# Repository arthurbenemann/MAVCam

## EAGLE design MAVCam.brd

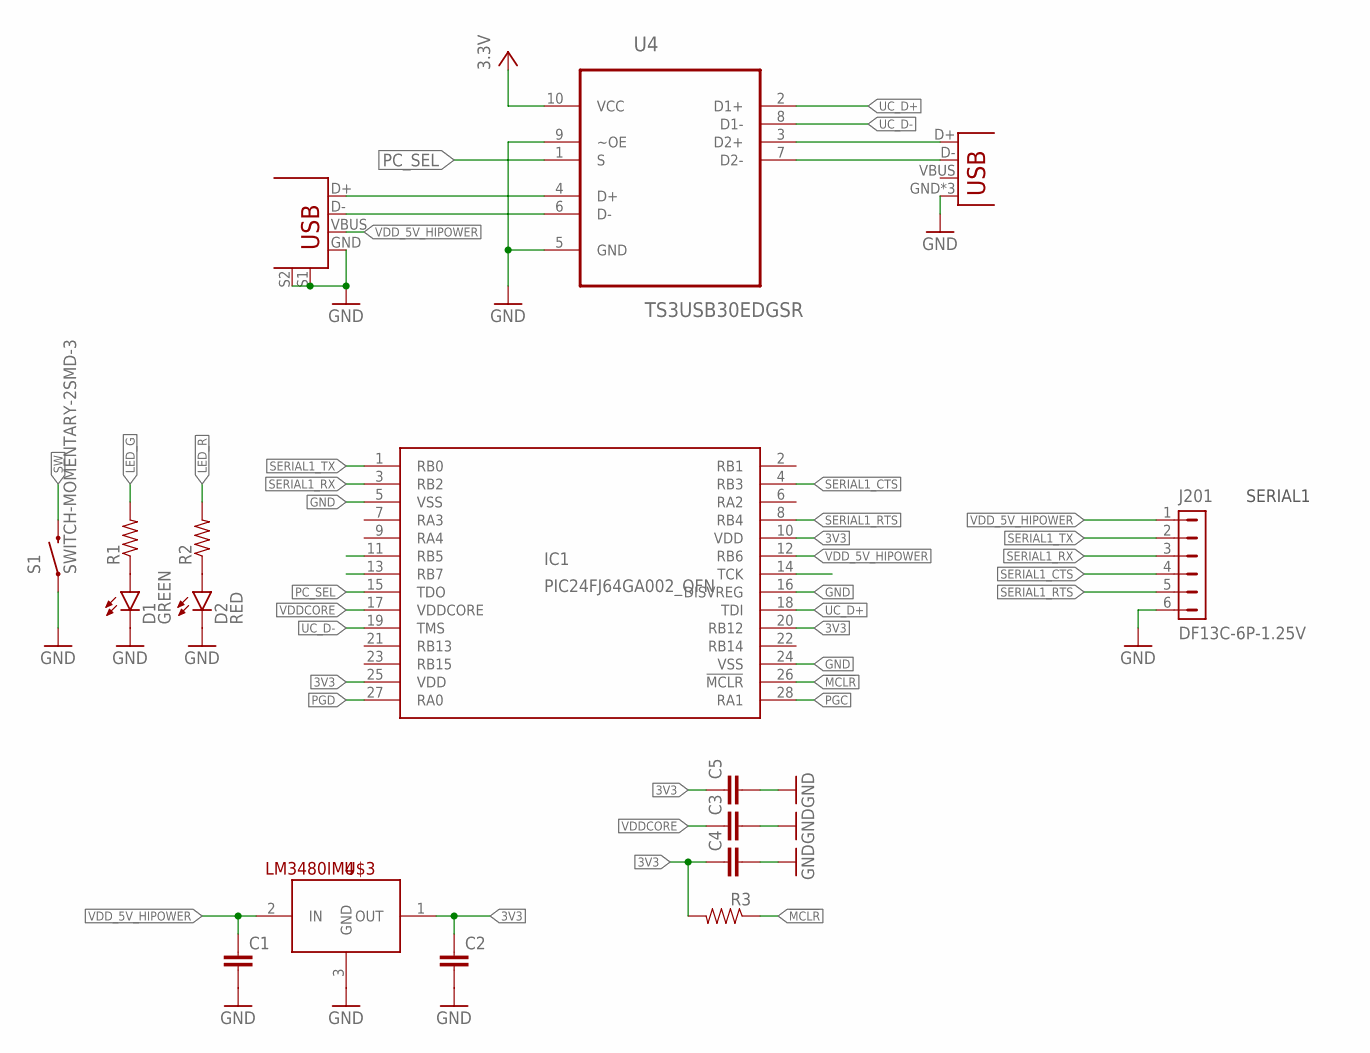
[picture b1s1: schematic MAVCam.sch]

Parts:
C1, C2, C3, C4, C5: CAP0603-CAP; 0603-CAP
D1: GREEN; LED-0603
D2: RED; LED-0603
IC1: PIC24FJ64GA002_QFN; QFN28-ML_6X6MM
J201: DF13C-6P-1.25V; PARTNO DF13C-6P-1.25V(20)
JP1: USB-MICROB
R1, R2, R3: RESISTOR0603-RES; 0603-RES
S1: SWITCH-MOMENTARY-2SMD-3; TACTILE_SWITCH_SMD-3
U4: TS3USB30EDGSR; SOP50P490X110-10N
U$1: USB+SHIELDUSB-A-S-NOSILK-FEMALE; USB-A-S-NOSILK-FEMALE
U$3: LM3480IM4; SOT23-3

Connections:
3V3: C2.1, C4.1, C5.1, IC1.10 (VDD), IC1.20 (RB12), IC1.25 (VDD), R3.2, U4.10 (VCC), U$3.1 (OUT)
!MCLR: IC1.26 (!MCLR), R3.1
GND: C1.2, C2.2, C3.2, C4.2, C5.2, D1.C, D2.C, IC1.5 (VSS), IC1.16 (DISVREG), IC1.24 (VSS), J201.6, JP1.GND, JP1.MT1 (GND), JP1.MT2 (GND), S1.1, U4.5 (GND), U4.9 (~OE), U$1.GND, U$1.S1, U$1.S2, U$3.3 (GND)
LED_G: IC1.13 (RB7), R1.2
LED_R: IC1.11 (RB5), R2.2
unnamed: U4.4 (D+), U$1.D+
unnamed: U4.6 (D-), U$1.D-
unnamed: D1.A, R1.1
unnamed: D2.A, R2.1
PC_D+: JP1.D+, U4.3 (D2+)
PC_D-: JP1.D-, U4.7 (D2-)
PC_SEL: IC1.15 (TDO), U4.1 (S)
PGC: IC1.28 (RA1)
PGD: IC1.27 (RA0)
SERIAL1_CTS: IC1.4 (RB3), J201.4
SERIAL1_RTS: IC1.8 (RB4), J201.5
SERIAL1_RX: IC1.3 (RB2), J201.3
SERIAL1_TX: IC1.1 (RB0), J201.2
SW: IC1.14 (TCK), S1.4 (2)
UC_D+: IC1.18 (TDI), U4.2 (D1+)
UC_D-: IC1.19 (TMS), U4.8 (D1-)
VDDCORE: C3.1, IC1.17 (VDDCORE)
VDD_5V_HIPOWER: C1.1, IC1.12 (RB6), J201.1, U$1.VBUS, U$3.2 (IN)

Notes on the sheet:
SERIAL1

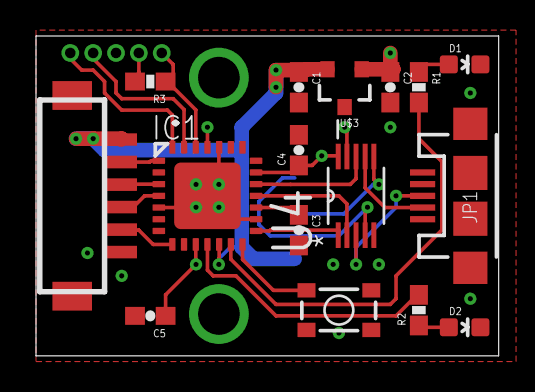
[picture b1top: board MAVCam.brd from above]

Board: 4 copper layers, 25.7 x 17.8 mm, 17 parts (1 on the bottom side), 21 nets.

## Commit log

2014-06-02 Finishing routing

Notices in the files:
parts and their libraries:
SparkFun-Connectors: Licensing: Creative Commons ShareAlike 4.0 International - https://creativecommons.org/licenses/by-sa/4.0
